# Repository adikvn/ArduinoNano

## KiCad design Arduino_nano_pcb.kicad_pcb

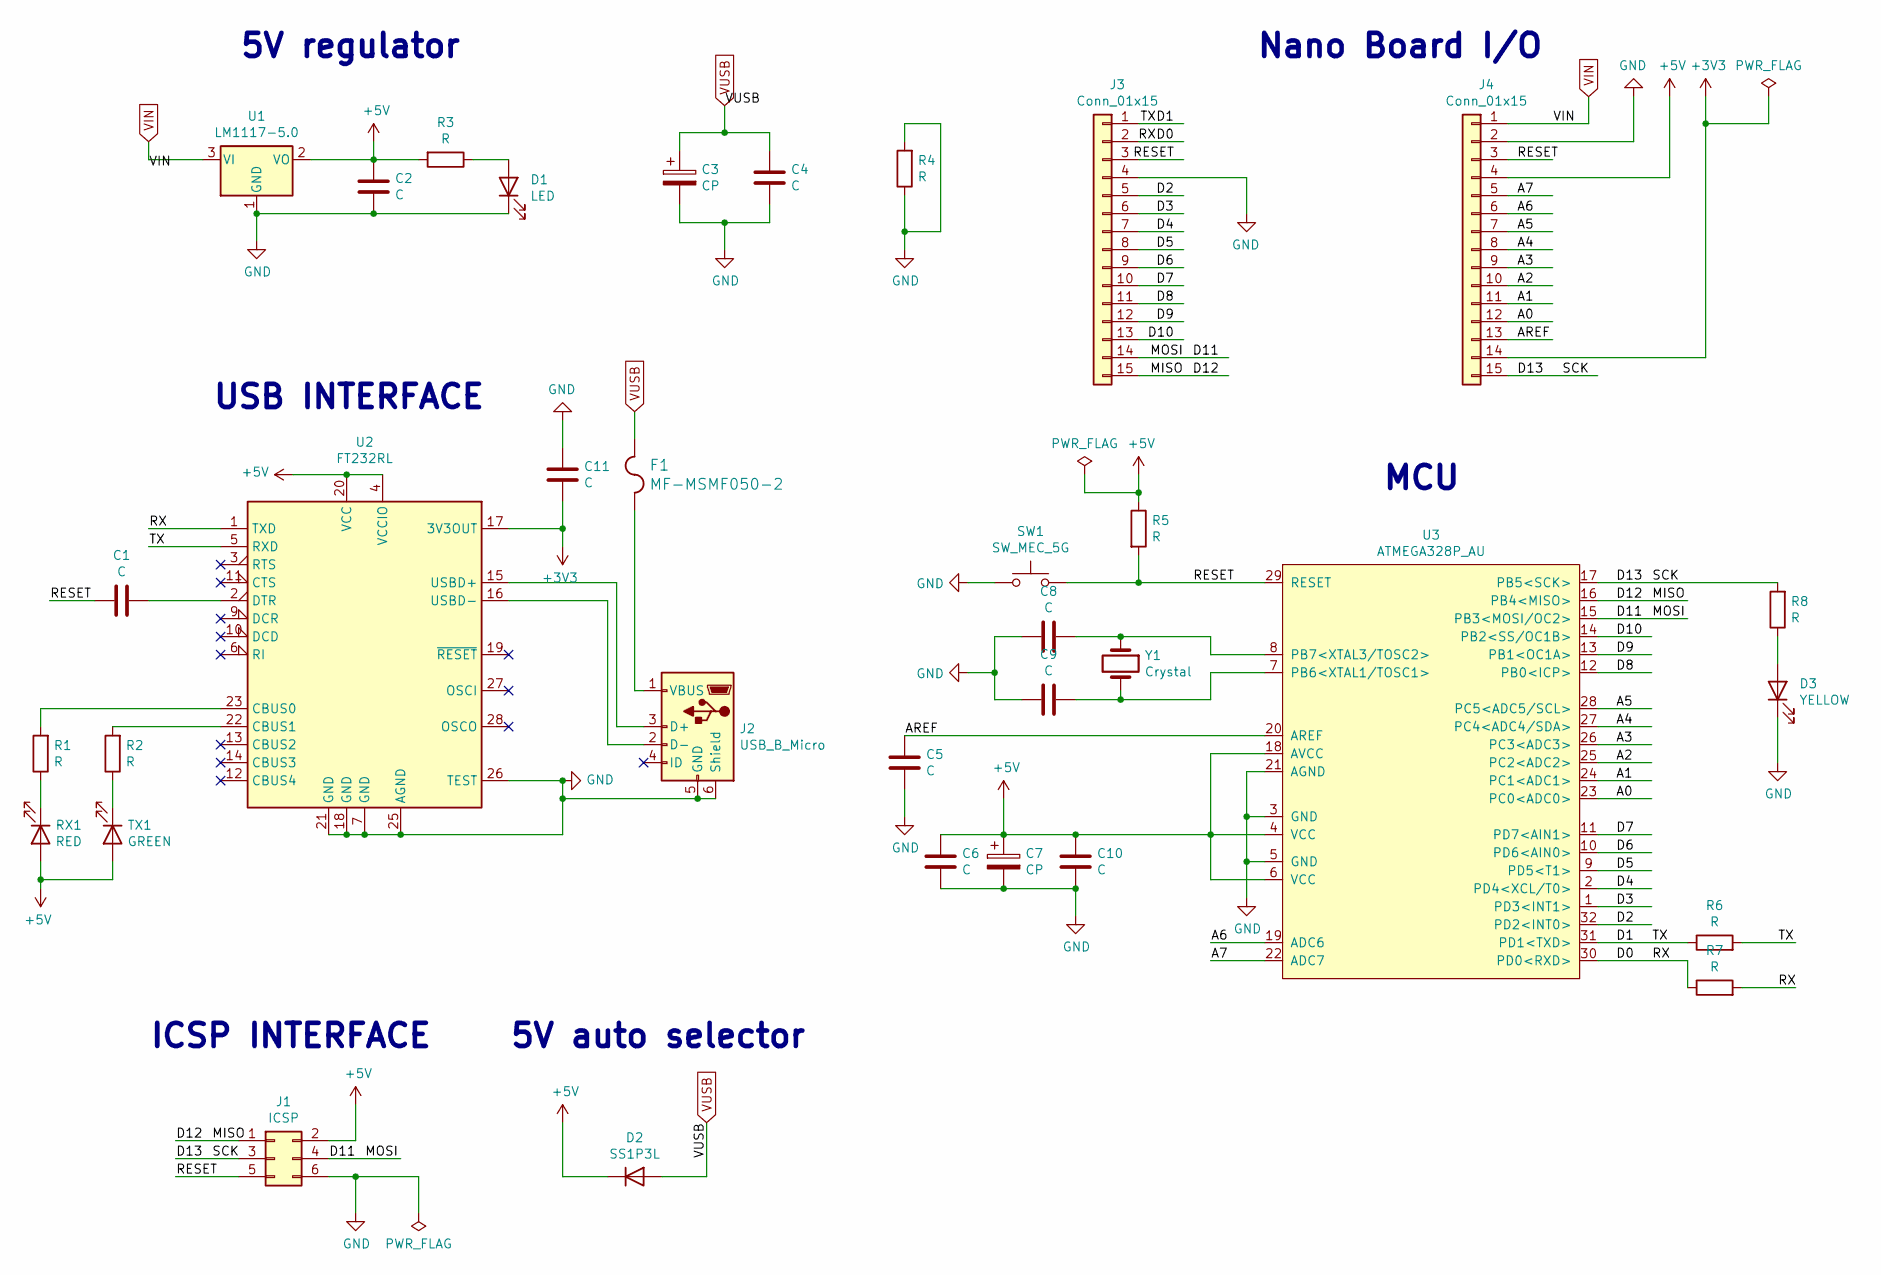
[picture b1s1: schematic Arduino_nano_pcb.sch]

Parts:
C1, C2, C4, C5, C6, C8, C9, C10, C11: C; C_0805_2012Metric
C3, C7: CP; C_0805_2012Metric
D1: LED; LED_0805_2012Metric
D2: SS1P3L; D_0805_2012Metric
D3: YELLOW; LED_0805_2012Metric
F1: MF-MSMF050-2
J1: ICSP; PinHeader_2x03_P2.54mm_Vertical
J2: USB_B_Micro; USB_Micro-B_Amphenol_10104110_Horizontal
J3, J4: Conn_01x15; PinHeader_1x15_P2.54mm_Vertical
R1, R2, R3, R4, R5, R6, R7, R8: R; R_0805_2012Metric
RX1: RED; LED_0805_2012Metric
SW1: SW_MEC_5G; SW_DIP_SPSTx01_Slide_6.7x4.1mm_W8.61mm_P2.54mm_LowProfile
TX1: GREEN; LED_0805_2012Metric
U1: LM1117-5.0; SOT-223-3_TabPin2
U2: FT232RL; SSOP-28_5.3x10.2mm_P0.65mm
U3: ATMEGA328P_AU; QFP32P80_1290X1290X120L90X22N
Y1: Crystal; Crystal_SMD_3215-2Pin_3.2x1.5mm

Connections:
+3V3: C11.1, J4.14, U2.17 (3V3OUT)
+5V: C2.1, C6.1, C7.1, C10.1, D2.1 (K), J1.2, J4.4, R3.2, R5.1, RX1.2 (A), TX1.2 (A), U1.2 (VO), U2.4 (VCCIO), U2.20 (VCC), U3.4 (VCC), U3.6 (VCC), U3.18 (AVCC)
/A0: J4.12, U3.23 (PC0<ADC0>)
/A1: J4.11, U3.24 (PC1<ADC1>)
/A2: J4.10, U3.25 (PC2<ADC2>)
/A3: J4.9, U3.26 (PC3<ADC3>)
/A4: J4.8, U3.27 (PC4<ADC4/SDA>)
/A5: J4.7, U3.28 (PC5<ADC5/SCL>)
/A6: J4.6, U3.19 (ADC6)
/A7: J4.5, U3.22 (ADC7)
/AREF: C5.1, J4.13, U3.20 (AREF)
/D0: J3.2, R7.1, R7.2, U2.1 (TXD), U3.30 (PD0<RXD>)
/D1: J3.1, R6.1, R6.2, U2.5 (RXD), U3.31 (PD1<TXD>)
/D2: J3.5, U3.32 (PD2<INT0>)
/D3: J3.6, U3.1 (PD3<INT1>)
/D4: J3.7, U3.2 (PD4<XCL/T0>)
/D5: J3.8, U3.9 (PD5<T1>)
/D6: J3.9, U3.10 (PD6<AIN0>)
/D7: J3.10, U3.11 (PD7<AIN1>)
/D8: J3.11, U3.12 (PB0<ICP>)
/D9: J3.12, U3.13 (PB1<OC1A>)
/D10: J3.13, U3.14 (PB2<SS/OC1B>)
/D11: J1.4, J3.14, U3.15 (PB3<MOSI/OC2>)
/D12: J1.1, J3.15, U3.16 (PB4<MISO>)
/D13: J1.3, J4.15, R8.2, U3.17 (PB5<SCK>)
/RESET: C1.2, J1.5, J3.3, J4.3, R5.2, SW1.3 (B), SW1.4 (B), U3.29 (RESET)
GND: C2.2, C3.2, C4.1, C5.2, C6.2, C7.2, C8.2, C9.2, C10.2, C11.2, D1.1 (K), D3.1 (K), J1.6, J2.5 (GND), J2.6 (Shield), J3.4, J4.2, R4.1, R4.2, SW1.1 (A), SW1.2 (A), U1.1 (GND), U2.7 (GND), U2.18 (GND), U2.21 (GND), U2.25 (AGND), U2.26 (TEST), U3.3 (GND), U3.5 (GND), U3.21 (AGND)
unnamed: C1.1, U2.2 (DTR)
unnamed: C8.1, U3.8 (PB7<XTAL3/TOSC2>), Y1.1
unnamed: C9.1, U3.7 (PB6<XTAL1/TOSC1>), Y1.2
unnamed: D1.2 (A), R3.1
unnamed: D3.2 (A), R8.1
unnamed: F1.2, J2.1 (VBUS)
unnamed: J2.2 (D-), U2.16 (USBD-)
unnamed: J2.3 (D+), U2.15 (USBD+)
unnamed: R1.1, RX1.1 (K)
unnamed: R1.2, U2.23 (CBUS0)
unnamed: R2.1, TX1.1 (K)
unnamed: R2.2, U2.22 (CBUS1)
VIN: J4.1, U1.3 (VI)
VUSB: C3.1, C4.2, D2.2 (A), F1.1

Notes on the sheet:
USB INTERFACE
ICSP INTERFACE
5V auto selector
Nano Board I/O
MCU
5V regulator

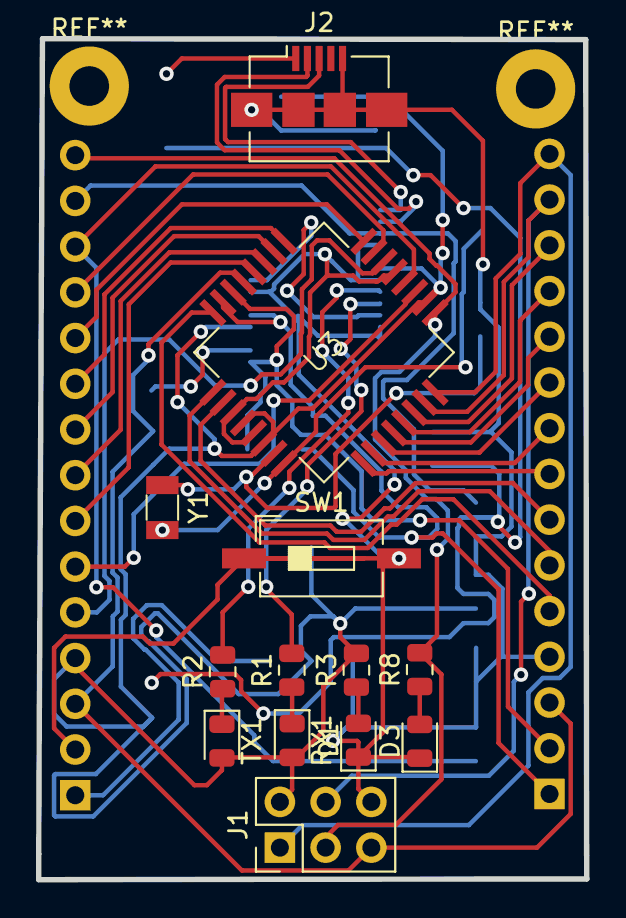
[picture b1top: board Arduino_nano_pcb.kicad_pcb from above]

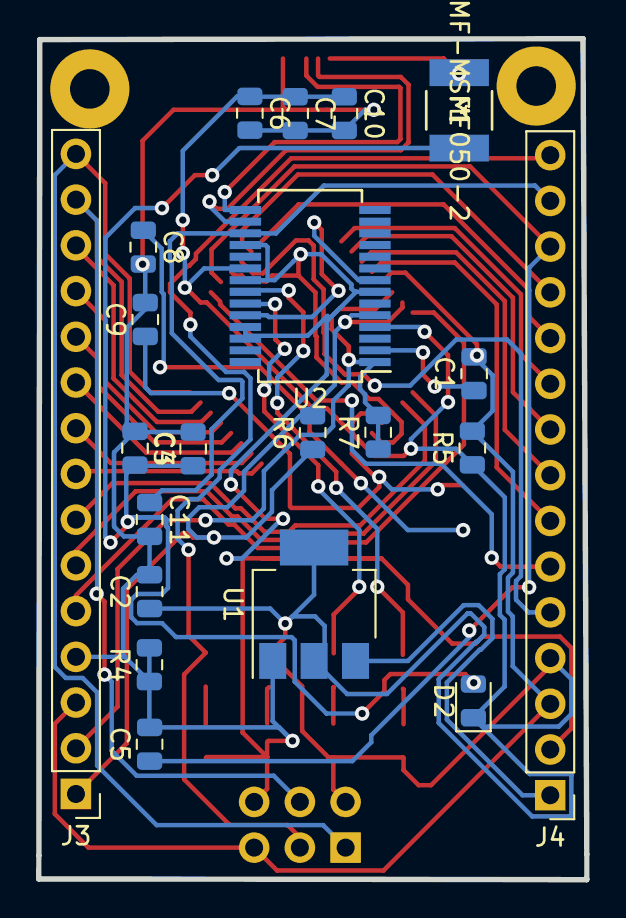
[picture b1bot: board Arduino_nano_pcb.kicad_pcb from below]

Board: 2 copper layers, 30.5 x 46.7 mm, 34 parts (21 on the bottom side), 41 nets.

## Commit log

2020-11-11 addfiles to main and change master to main
2020-11-11 gitignore fix

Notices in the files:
parts and their libraries:
Copyright 2016 Accelerated Designs. All rights reserved.
